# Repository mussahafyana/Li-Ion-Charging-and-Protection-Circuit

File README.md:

# Li-Ion Charging and Protection Circuit

## Overview

This project presents a lithium-ion battery charging and protection circuit designed in **KiCad**. The circuit combines charging control, battery protection, status indication, and MOSFET-based isolation for safer battery operation.

## Key Components

### TP4056-42-ESOP8 Charging Controller
The **TP4056** provides constant-current/constant-voltage (CC/CV) charging for a lithium-ion cell using a 5 V input.

- Controls the battery charging process
- Uses the **RPROG resistor** to configure charging current
- Provides **CHRG** and **STDBY** outputs for charging-status indication

### DW01A Battery Protection IC
The **DW01A** monitors the battery and provides protection against unsafe operating conditions, including:

- Overcharge
- Over-discharge
- Overcurrent
- Short-circuit conditions

### N-Channel MOSFET Protection Stage
Two N-channel MOSFETs are controlled by the DW01A and act as electronic switches to disconnect the battery during abnormal operating conditions.

### Charging Status LEDs
Red and green LEDs are connected to the TP4056 status outputs to provide visual indication of the charging state.

### Micro-USB Input
A Micro-USB connector provides the 5 V input supply for the charging circuit.

## Design Features

- Lithium-ion CC/CV charging
- Overcharge protection
- Over-discharge protection
- Overcurrent protection
- Short-circuit protection
- MOSFET-based battery isolation
- Charging-status indication
- Micro-USB charging input

## Tools & Technologies

- KiCad
- Schematic Capture
- Power Electronics
- Lithium-Ion Battery Management
- Electronic Circuit Design

## Schematic

The complete lithium-ion charging and protection circuit is shown below.

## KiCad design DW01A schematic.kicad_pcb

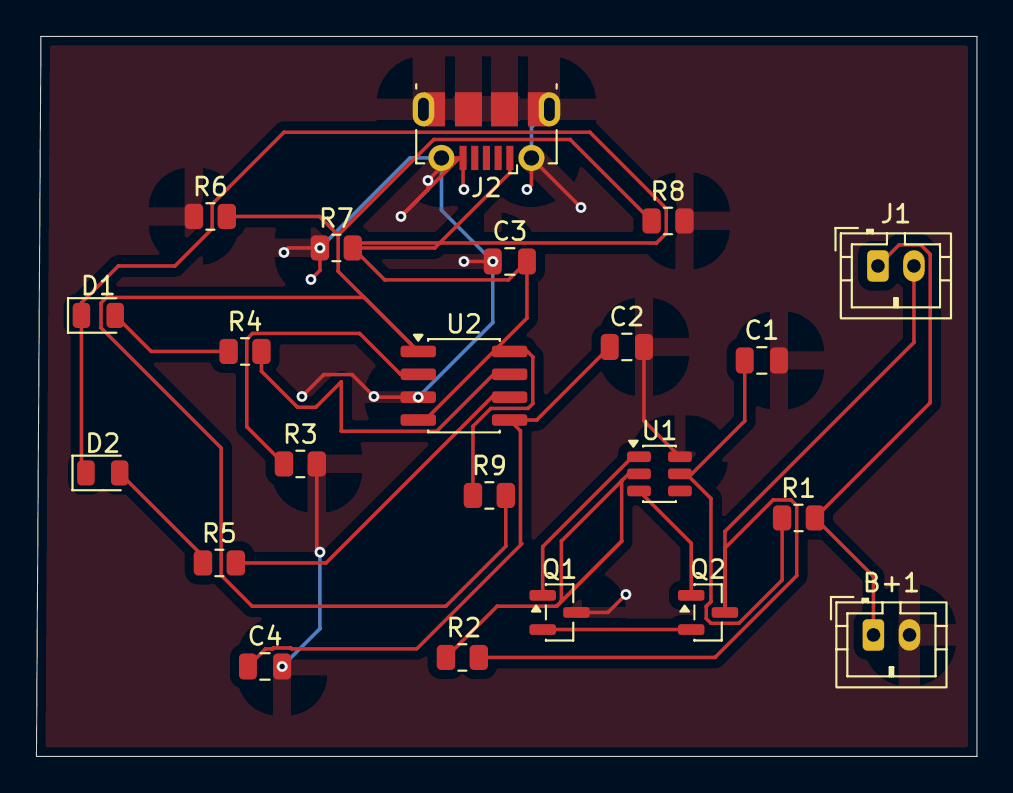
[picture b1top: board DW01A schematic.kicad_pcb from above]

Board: 2 copper layers, 52.2 x 40.0 mm, 22 parts (0 on the bottom side), 16 nets.

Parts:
B+1: B-; JST_PH_B2B-PH-K_1x02_P2.00mm_Vertical
C1: 0.1u; C_0805_2012Metric
C2, C3: 10uF; C_0805_2012Metric
C4: Bat-; C_0805_2012Metric
D1: RedLED; LED_0805_2012Metric
D2: Green LED; LED_0805_2012Metric
J1: Conn_01x02; JST_PH_B2B-PH-K_1x02_P2.00mm_Vertical
J2: USB_B_Micro; USB_Micro-B_Molex-105017-0001
Q1, Q2: Q_NMOS_GDS; SOT-23
R1: 470; R_0805_2012Metric
R2: 2K; R_0805_2012Metric
R3: Rprog; R_0805_2012Metric
R4, R5: 1K; R_0805_2012Metric
R6: NTC; R_0805_2012Metric
R7: 0.0004K; R_0805_2012Metric
R8: R2; R_0805_2012Metric
R9: R1; R_0805_2012Metric
U1: DW01A; SOT-23-6
U2: TP4056-42-ESOP8; SOP-8_3.76x4.96mm_P1.27mm

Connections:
GND: B+1.2 (-), C1.2, C2.2, C3.1, C4.2, J2.5 (GND), J2.6 (Shield), Q1.3 (S), R3.2, R6.1, R7.1, R8.2, U1.6 (GND), U2.3 (GND)
unnamed: D1.2 (A), R4.1
unnamed: C3.2, D1.1 (K), D2.1 (K), J2.1 (VBUS), R7.2, R9.1, U2.4 (V_{CC}), U2.8 (CE)
unnamed: D2.2 (A), R5.1
unnamed: Q1.2 (D), Q2.2 (D)
unnamed: Q1.1 (G), U1.1 (OD)
unnamed: Q2.1 (G), U1.3 (OC)
unnamed: R2.1, U1.2 (CS)
unnamed: C1.1, R1.1, U1.5 (VCC)
unnamed: C2.1, C4.1, U2.5 (BAT)
unnamed: R3.1, U2.2 (PROG)
unnamed: R6.2, R8.1, R9.2, U2.1 (TEMP)
unnamed: R4.2, U2.7 (~CHRG)
unnamed: R5.2, U2.6 (~STDBY)
P+: B+1.1 (+), J1.1, R1.2
P-: J1.2, Q2.3 (S), R2.2
